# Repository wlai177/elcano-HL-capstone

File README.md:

View this project on [CADLAB.io](https://cadlab.io/node/765). 

# elcano-HL-capstone
Repo for the Elcano high-level redesign project (BEE capstone project)

The Elcano High-Level system is responsible for setting a desired vehicle speed and direction based on localization, pathfinding, and obstacle detection. The Low-Level system then has the job of making the vehicle execute the desired commands. At present, the High-Level system is partitioned among several processors:
· C7 (Raspberry Pi) processes visual information
· C6 (Arduino Mega) localization based on GPS, speed, and INU
· C5 (Arduino Micro) Lidar/sonar obstacle detection
· C4 (Arduino Mega) computes path from digital map
· C3 (Arduino Micro) processes all data and sends instructions to Low-Level

The High-Level Redesign project seeks to port the C6, C4, and C3 processors to a single Arduino DUE. The new processor is designated as the C643 processor and has the following features:
· Elcano Low-Level Backwards Compatibility
· Simplified Serial Communication
· Single Processor Operation
· Arduino IDE Friendly
· Smaller Footprint
· CAN Bus Support
· 32-bit processing

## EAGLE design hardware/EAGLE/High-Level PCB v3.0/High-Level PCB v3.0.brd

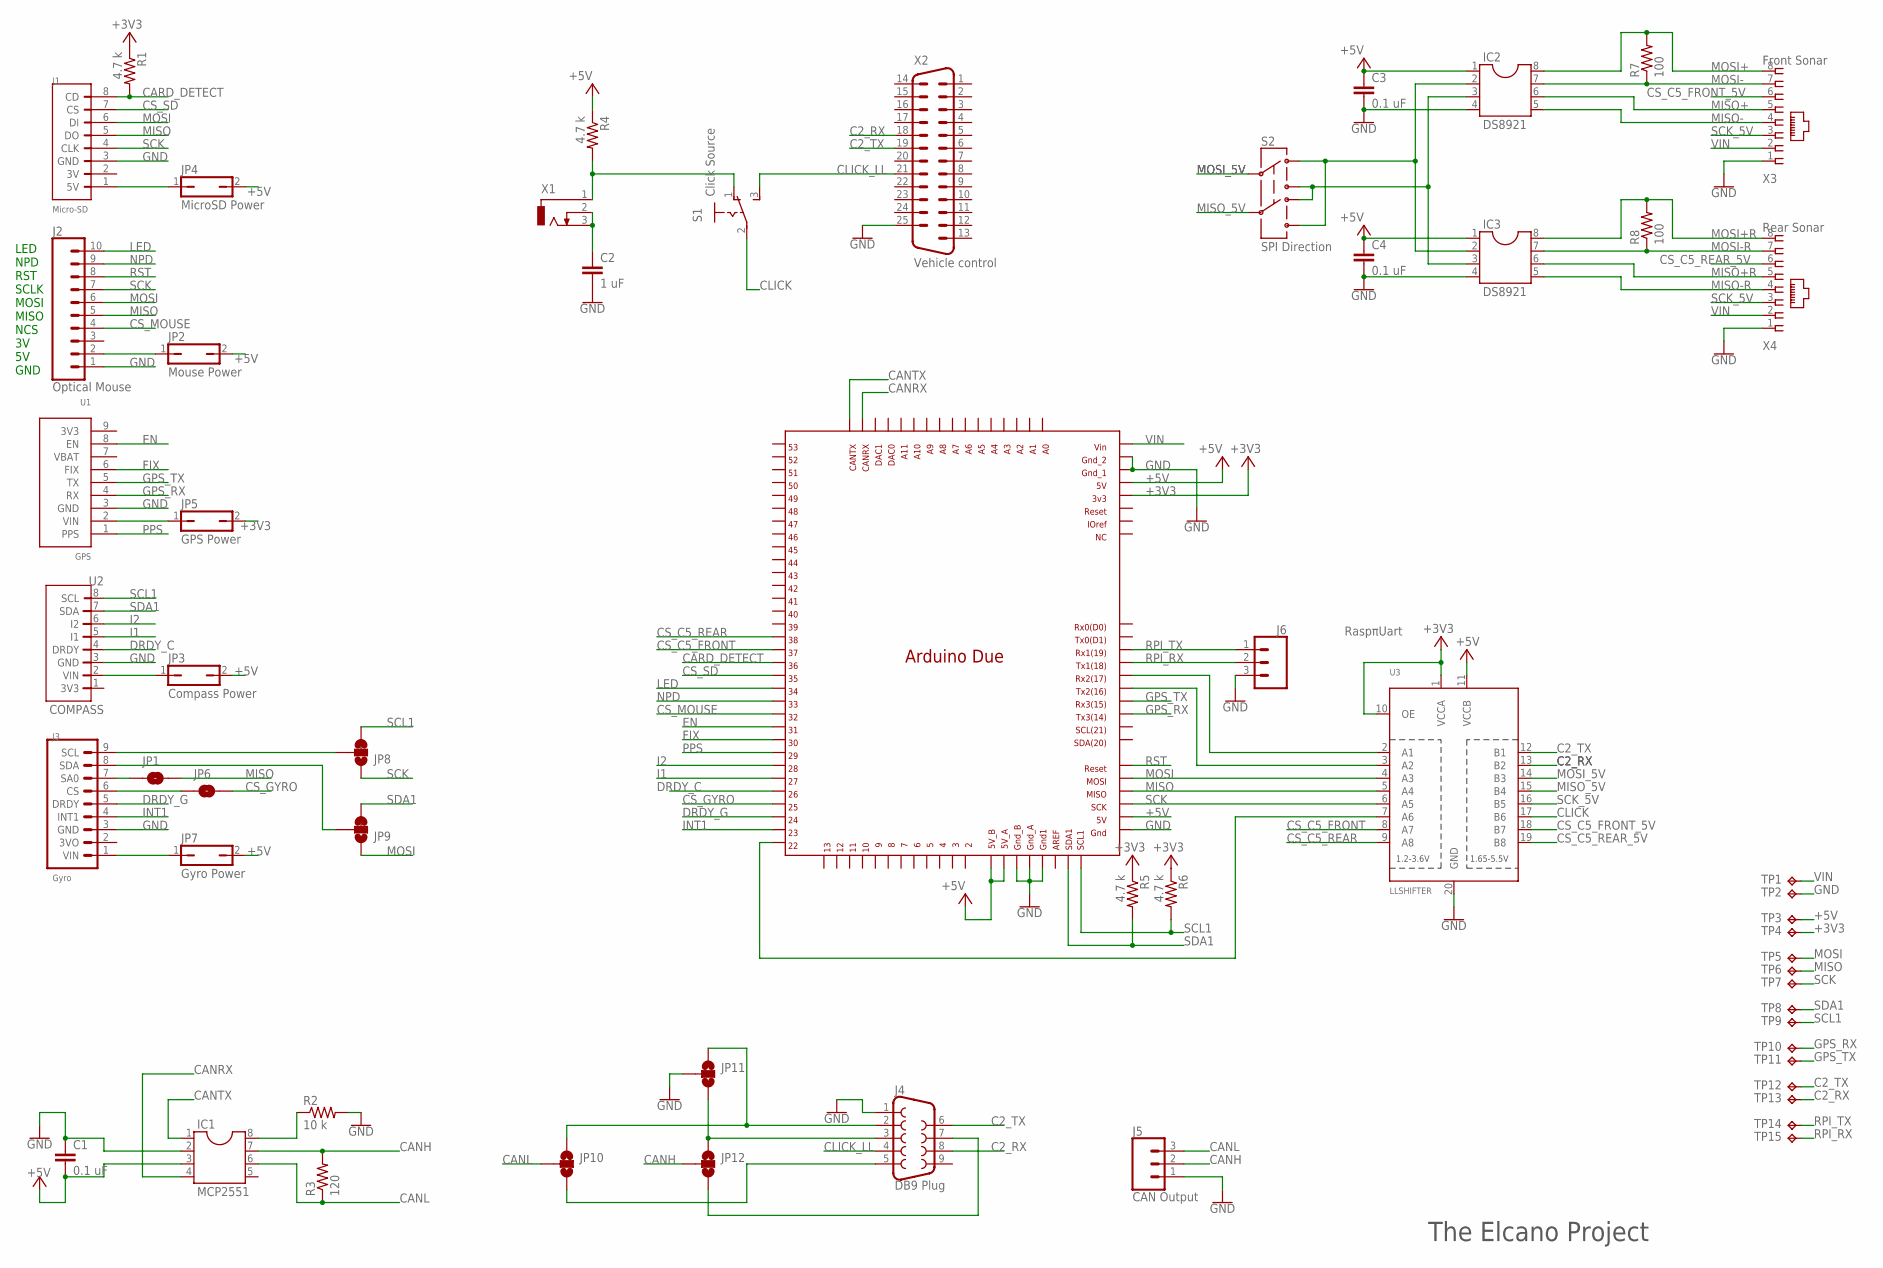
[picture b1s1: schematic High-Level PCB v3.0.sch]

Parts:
C1, C3, C4: 0.1 uF; C2.5-5
C2: 1 uF; C2.5-5
IC1: MCP2551; DIL08
IC2, IC3: DS8921; DIL08
J1: Micro-SD; ELSDCARD
J2: Optical Mouse; 1X10
J3: Gyro; ELGYRO
J4: DB9 Plug; DB9_MALE
J5: CAN Output; SCREWTERMINAL-5MM-3
J6: RaspπUart; 1X03
JP1, JP6: JUMPER-SMT_2_NO_SILK; SMT-JUMPER_2_NO_SILK
JP2: Mouse Power; JP1
JP3: Compass Power; JP1
JP4: MicroSD Power; JP1
JP5: GPS Power; JP1
JP7: Gyro Power; JP1
JP8, JP9: JUMPER-SMT_3_1-NC_TRACE_SILK; SMT-JUMPER_3_1-NC_TRACE_SILK
JP10, JP11, JP12: JUMPER-SMT_3_NO_SILK; SMT-JUMPER_3_NO_SILK
MCU1: DUE(NORMAL)
R1, R4, R5, R6: 4.7 k; 0204/7
R2: 10 k; 0204/7
R3: 120; 0204/7
R7, R8: 100; 0204/7
S1: Click Source; 255SB
S2: SPI Direction; DPDT
TP1, TP2, TP3, TP4, TP5, TP6, TP7, TP8, TP9, TP10, TP11, TP12, TP13, TP14, TP15: TPPAD1-17; P1-17
U1: GPS; ELGPS
U2: COMPASS; ELCOMPASS
U3: LLSHIFTER; ELSHIFTER
X1: 2.5MMJACK
X2: Vehicle control; M25H
X3: Front Sonar; RJ45-NO-SHIELD
X4: Rear Sonar; RJ45-NO-SHIELD

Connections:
+3V3: JP5.2, MCU1.3V3, R1.1, R5.1, R6.1, TP4.TP, U3.1 (VCCA), U3.10 (OE)
+5V: C1.2, C3.1, C4.1, IC1.3, IC2.1, IC3.1, JP2.2, JP3.2, JP4.2, JP7.2, MCU1.5V, MCU1.5V_A, MCU1.5V_B, MCU1.GND_ICSP, R4.1, TP3.TP, U3.11 (VCCB)
C2_RX: J4.8, TP13.TP, U3.13 (B2), X2.18
C2_TX: J4.6, TP12.TP, U3.12 (B1), X2.19
CANH: IC1.7, J5.2, JP12.2, R3.2
CANL: IC1.6, J5.3, JP10.2, R3.1
CANRX: IC1.4, MCU1.CANRX
CANTX: IC1.1, MCU1.CANTX
CARD_DETECT: J1.8 (CD), MCU1.36, R1.2
CLICK: S1.2, U3.17 (B6)
CLICK_LL: J4.4, S1.3 (S), X2.21
CS_C5_FRONT: MCU1.37, U3.8 (A7)
CS_C5_FRONT_5V: U3.18 (B7), X3.6
CS_C5_REAR: MCU1.38, U3.9 (A8)
CS_C5_REAR_5V: U3.19 (B8), X4.6
CS_GYRO: JP6.2, MCU1.25
CS_MOUSE: J2.4, MCU1.32
CS_SD: J1.7 (CS), MCU1.35
DRDY_C: MCU1.26, U2.4 (DRDY)
DRDY_G: J3.5 (DRDY), MCU1.24
EN: MCU1.31, U1.8 (EN)
FIX: MCU1.30, U1.6 (FIX)
GND: C1.1, C2.2, C3.2, C4.2, IC1.2, IC2.4, IC3.4, J1.3 (GND), J2.1, J3.3 (GND), J4.1, J5.1, J6.3, JP11.2, MCU1.5V_ICSP, MCU1.GND1, MCU1.GND_1, MCU1.GND_2, MCU1.GND_A, MCU1.GND_B, R2.2, TP2.TP, U1.3 (GND), U2.3 (GND), U3.20 (GND), X2.25, X3.1, X4.1
GPS_RX: MCU1.TX3, TP10.TP, U1.4 (RX)
GPS_TX: MCU1.RX3, TP11.TP, U1.5 (TX)
I1: MCU1.27, U2.5 (I1)
I2: MCU1.28, U2.6 (I2)
INT1: J3.4 (INT1), MCU1.23
LED: J2.10, MCU1.34
MISO: J1.5 (DO), J2.5, JP1.2, MCU1.MISO_ICSP, TP6.TP, U3.5 (A4)
MISO+: IC2.6, X3.5
MISO+R: IC3.6, X4.5
MISO-: IC2.5, X3.4
MISO-R: IC3.5, X4.4
MISO_5V: S2.5, U3.15 (B4)
MOSI: J1.6 (DI), J2.6, JP9.1, MCU1.MOSI_ICSP, TP5.TP, U3.4 (A3)
MOSI+: IC2.8, R7.2, X3.8
MOSI+R: IC3.8, R8.2, X4.8
MOSI-: IC2.7, R7.1, X3.7
MOSI-R: IC3.7, R8.1, X4.7
MOSI_5V: S2.2, U3.14 (B3)
unnamed: C2.1, X1.2, X1.3
unnamed: IC2.2, IC3.2, S2.1, S2.6
unnamed: IC2.3, IC3.3, S2.3, S2.4
unnamed: MCU1.TX2, U3.3 (A2)
unnamed: MCU1.RX2, U3.2 (A1)
unnamed: R4.2, S1.1 (O), X1.1
unnamed: JP3.1, U2.2 (VIN)
unnamed: J3.1 (VIN), JP7.1
unnamed: J1.1 (5V), JP4.1
unnamed: J4.3, JP11.3, JP12.1
unnamed: MCU1.22, U3.7 (A6)
unnamed: J2.2, JP2.1
unnamed: JP5.1, U1.2 (VIN)
unnamed: J4.5, JP10.3
unnamed: J4.7, JP12.3
unnamed: IC1.8, R2.1
unnamed: J4.2, JP10.1, JP11.1
unnamed: J3.6 (CS), JP6.1
unnamed: J3.7 (SA0), JP1.1
unnamed: J3.8 (SDA), JP9.2
unnamed: J3.9 (SCL), JP8.2
NPD: J2.9, MCU1.33
PPS: MCU1.29, U1.1 (PPS)
RPI_RX: J6.2 (1), MCU1.TX1, TP15.TP
RPI_TX: J6.1 (2), MCU1.RX1, TP14.TP
RST: J2.8, MCU1.RESET_ICSP
SCK: J1.4 (CLK), J2.7, JP8.1, MCU1.SCK_ICSP, TP7.TP, U3.6 (A5)
SCK_5V: U3.16 (B5), X3.3, X4.3
SCL1: JP8.3, MCU1.SCL1, R6.2, TP9.TP, U2.8 (SCL)
SDA1: JP9.3, MCU1.SDA1, R5.2, TP8.TP, U2.7 (SDA)
VIN: MCU1.VIN, TP1.TP, X3.2, X4.2

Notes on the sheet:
LED NPD RST SCLK MOSI MISO NCS 3V 5V GND
The Elcano Project

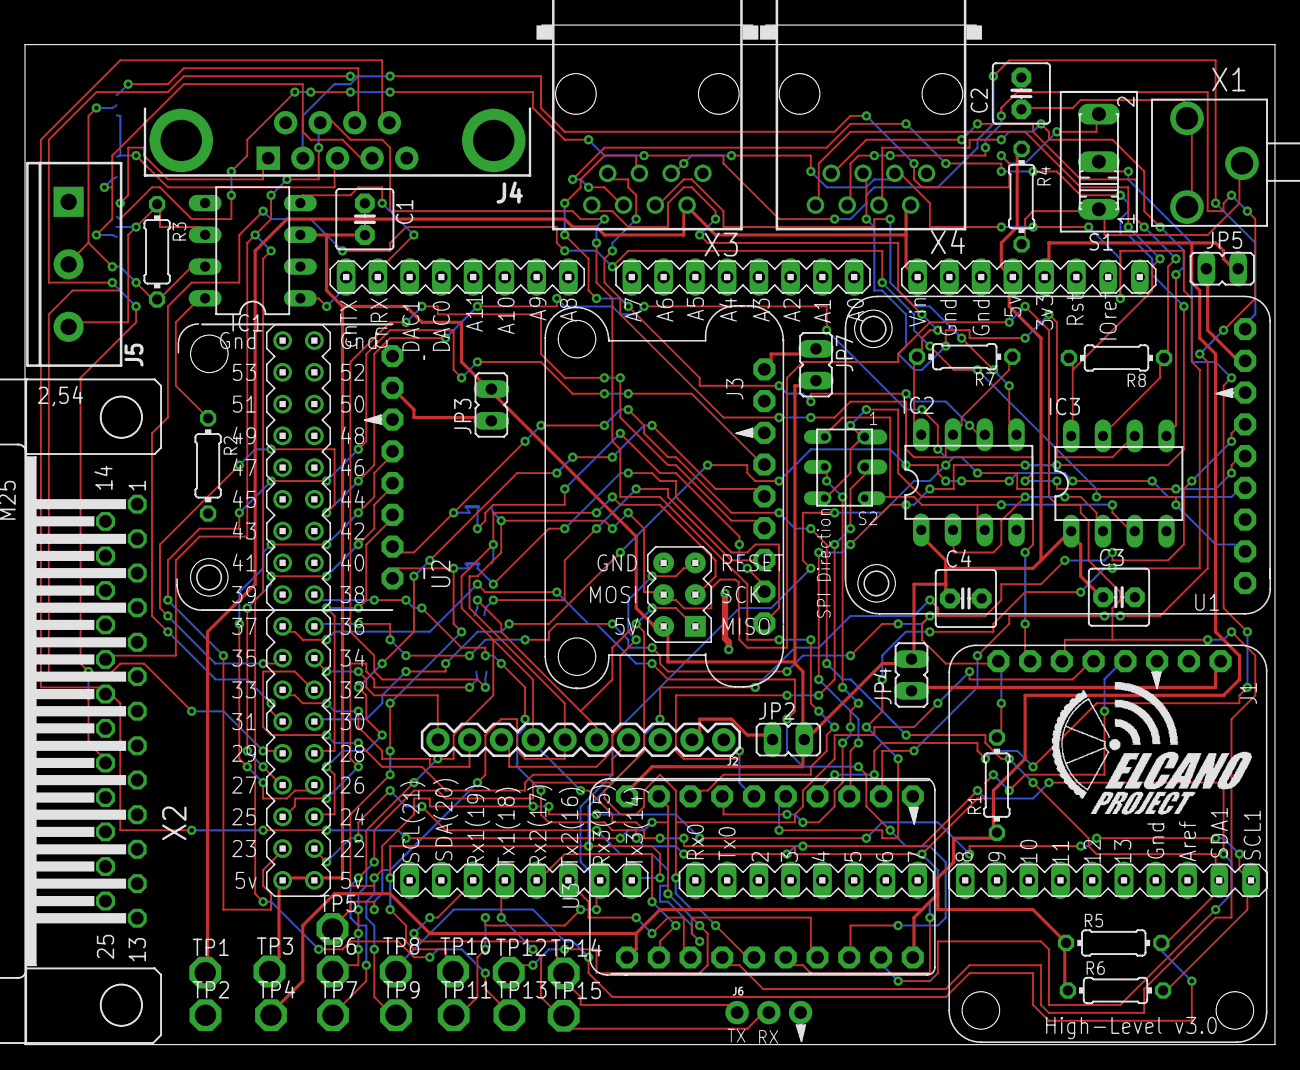
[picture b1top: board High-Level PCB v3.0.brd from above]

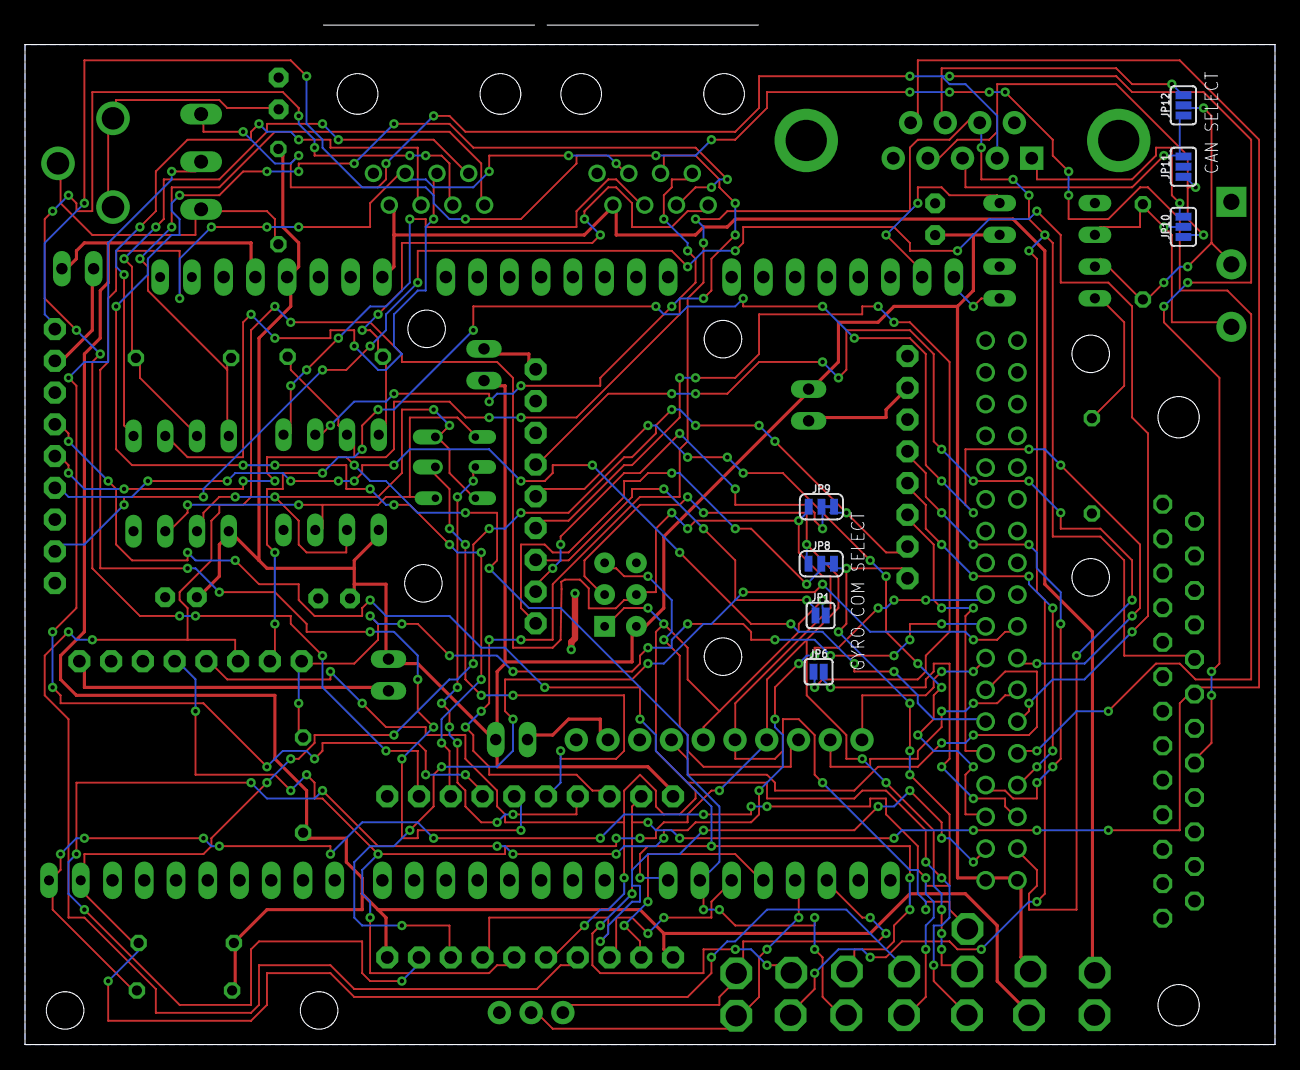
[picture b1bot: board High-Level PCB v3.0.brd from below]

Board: 2 copper layers, 100.0 x 81.6 mm, 58 parts (7 on the bottom side), 72 nets.

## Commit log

2018-03-15 Backlink to CADLAB.io has been added.
2018-03-15 Uploaded initial sch
    Baseline sch that was submitted in the Design Doc
2018-03-15 Moved sch to a new folder
2018-03-16 Libraries for the compass sensor
    Libraries for the LSM303 Compass sensor from adafruit
    Product: https://www.adafruit.com/product/1120
2018-03-16 Create sample text
2018-03-21 Added gyro library
2018-03-21 Moved files from OneDrive
2018-03-21 Added image of draft schematic
    Accurate as of March 10th
2018-03-21 Added external spec info to the Readme
2018-03-21 Added/Modified schematic images
    For those who don't have Eagle installed, these images will allow you to view the schematics.
2018-03-22 Create Highlevel-Periperals_Tester
2018-03-26 Added library for RJ45 connector
2018-03-26 Optical Mouse testing Code
    Got it to work by comenting out lines 40-43. It bypasses the product ID.
2018-03-28 WireModification
    L3Gd20_U and LSM303DLHC are no longer adafruit standard libraries.
    replaced all instances of Wire with Wire1
    Due can't work with multiple I2C if SCL 1and SDA1 are used. Note SCL1 and SDA1 need pull up resistors.
2018-03-29 Added additional header for compass and moved the i2C to other bus
2018-03-29 Fixed pull-up resistors on I2C bus
2018-03-29 Removed old sch and added newer version
2018-03-30 Added code to test UART communication
2018-04-05 Added CAN bus chip (MCP2551)
2018-04-06 Added DB9 and terminal block connectors
2018-04-08 Voltage level shifter adafruit
    Removed Sparkfun voltage level shifter and replaced with adafruit's
2018-04-11 Moved some stuff around and re-routed the logic converter chip
2018-04-11 Added Test Points
2018-04-16 Added some changes (see description)
    Added EN for GPS
    Added CD for microSD
    Cleaned up breakout headers
    Need to connect solder jumpers
2018-04-16 Added larger frame
2018-04-16 Added SPI connection for the Gyro
2018-04-16 Re-arranged pin connections on DUE
2018-04-16 Fixed duplicated I2C lines on the gyro header
2018-04-16 Changed "DUE Shield" label to "Arduino Due"
2018-04-17 Added Test Points for +5V and +3V3
2018-04-22 Add files via upload
    FootPrint for AdaFruit GPS.
2018-04-23 Add files via upload
    TXB0108 adafruit footprint.
2018-04-26 Add files via upload
    ADAFRUIT LSM303 COMPASS breakout board footprint.
2018-04-26 footprints
    foot print updates
2018-04-26 Add files via upload
    Added uart connection for raspberrypi
2018-04-26 Add files via upload
    footprint for raspberry pi connection
2018-04-27 raspberry pi foot prints and compass mods. Added tx, rx lines in schematic for raspberry pi
    raspberry pi foot prints and compass mods.
    Added tx, rx lines in schematic for raspberry pi
2018-04-27 Added footprint for new audio jack
2018-04-29 ElCano breakoutboard footprints.
    Contains footprints in one easy to find package.
2018-04-29 added footprints
    Includes footprints for all breakout boards except optical mouse
2018-04-29 Added Micro Sd breakout board.
    Added Micro Sd breakout board.
2018-05-02 Removed junk file
2018-05-02 Used larger resistor footprints
2018-05-03 Added correct RJ45 footprints
2018-05-03 drill hole changes
    standarized screw hole to 3mm
2018-05-03 Removed second Compass
2018-05-03 due silk screen fix
    fixed hole move silk screening
2018-05-03 changes
    Changed DPDT. Updated with new Due library where the silk screen has been moved.
    Solved drill hole issue with Due library
2018-05-04 Copied sch to backup folder
2018-05-04 Added Board and fixed Test Points
    Added the BRD file and fixed GPS test points and added test points for Raspberry UART
2018-05-04 Started board layout
2018-05-04 breakout holes
    Fixed hole size for the breakout boards. Should be 3mm for all
2018-05-05 100% autoroute success
2018-05-06 Added "Test" folder with a high ground pour board varient
2018-05-06 SilkSCreen print remove
    Removed Debug pins from Arduino Due
    Removed SilkScreen print from breakoutboards
2018-05-06 Add files via upload
    Breakout boards have 3mm holes.
    Removed silkscreen print from breakout boards.
    Updated New arduino due it doesn't have the debug pins.
2018-05-07 Backuped the 100% auto route brd
2018-05-08 Added two more autoroute test
    Board 2 looks decent
2018-05-09 Tried adding thicker power traces
    Has air wires!
2018-05-10 The 3 board has no air wires!
    And it has thick power traces.
2018-05-10 Added Gerber files
2018-05-11 Added a silk screen logo
2018-05-13 Added and moved some silkscreen labels
2018-05-13 Moved files around
    Current PCB files are moved one level up
2018-05-13 Generated Gerbers
    PCB rendered provided by JLC PCB
2018-05-13 Updated png image of the v3 HL board
2018-05-15 Create High-level-libraries
2018-05-15 Create h
2018-05-15 Create hi
2018-05-16 Create n
2018-05-16 Fixed Click signal and made new gerbers
    Click signals from the low level systems are now tied together.
2018-05-16 Fixed SPST size and generated new Gerbers
2018-05-23 Added a Bill of Materials BOM
2018-06-03 Updated BOM

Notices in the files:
parts and their libraries:
SparkFun-Connectors: Licensing: Creative Commons ShareAlike 4.0 International - https://creativecommons.org/licenses/by-sa/4.0
